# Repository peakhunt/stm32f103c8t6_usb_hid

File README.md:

# stm32f103c8t6_usb_hid

This is a USB joystick demo using STM32F103C8T6.
The whole project was developed using CubeMX.

## hardware
Basically I used very cheap chinese STM32F103 module. [The link is here][1]

As for arcade style joysticks and push buttons, there are a bunch of
cheap chinese stuffs out there.

As for connection, please refer to the kicad directory. It's gonna cost about $10 US dollars to get the 10 custom PCBs from cheap PCB manufactureres. Whether you use custom soldering or PCB based approach, just be sure to pay attention to the capacitor to prevent debouncing .  And just bear in mind that I am a S/W enginner. Designing a simple H/W like this is just a kind of my hobby.

[1]: https://www.aliexpress.com/item/Free-Shipping-STM32F103C8T6-ARM-STM32-Minimum-System-Development-Board-Module-For-arduino/32555258029.html?spm=2114.search0104.3.89.mrWsfD&ws_ab_test=searchweb0_0,searchweb201602_5_5460015_10152_10065_10151_10068_5470015_10307_10137_10060_10155_10154_10056_10055_10054_10059_100031_10099_10338_10339_5380015_10103_10102_440_10052_10053_10142_10107_10050_10051_10326_10084_10083_10080_10082_10081_10110_10175_10111_10112_10113_10114_143_10037_10312_10313_10314_10078_10079_10077_10073,searchweb201603_19,ppcSwitch_5&btsid=67a13b36-0190-4c70-9deb-1a2744050228&algo_expid=c62760bd-a140-4c3e-86ec-c725bdf3f0dc-14&algo_pvid=c62760bd-a140-4c3e-86ec-c725bdf3f0dc

## my build
Here is a demo joystick I built. I've been having some fun using it with retroarch. I love kungfu master.

The case is actually a small rectangular plastic container ( or basket or whatever). I bought it at less than 2 dollars at a local store and drilled it.

Here is the image of PCB I created for the build. It's really primitive simple board and anybody can do it. I just hated all the stupid fragile wiring I had to do before the PCB.

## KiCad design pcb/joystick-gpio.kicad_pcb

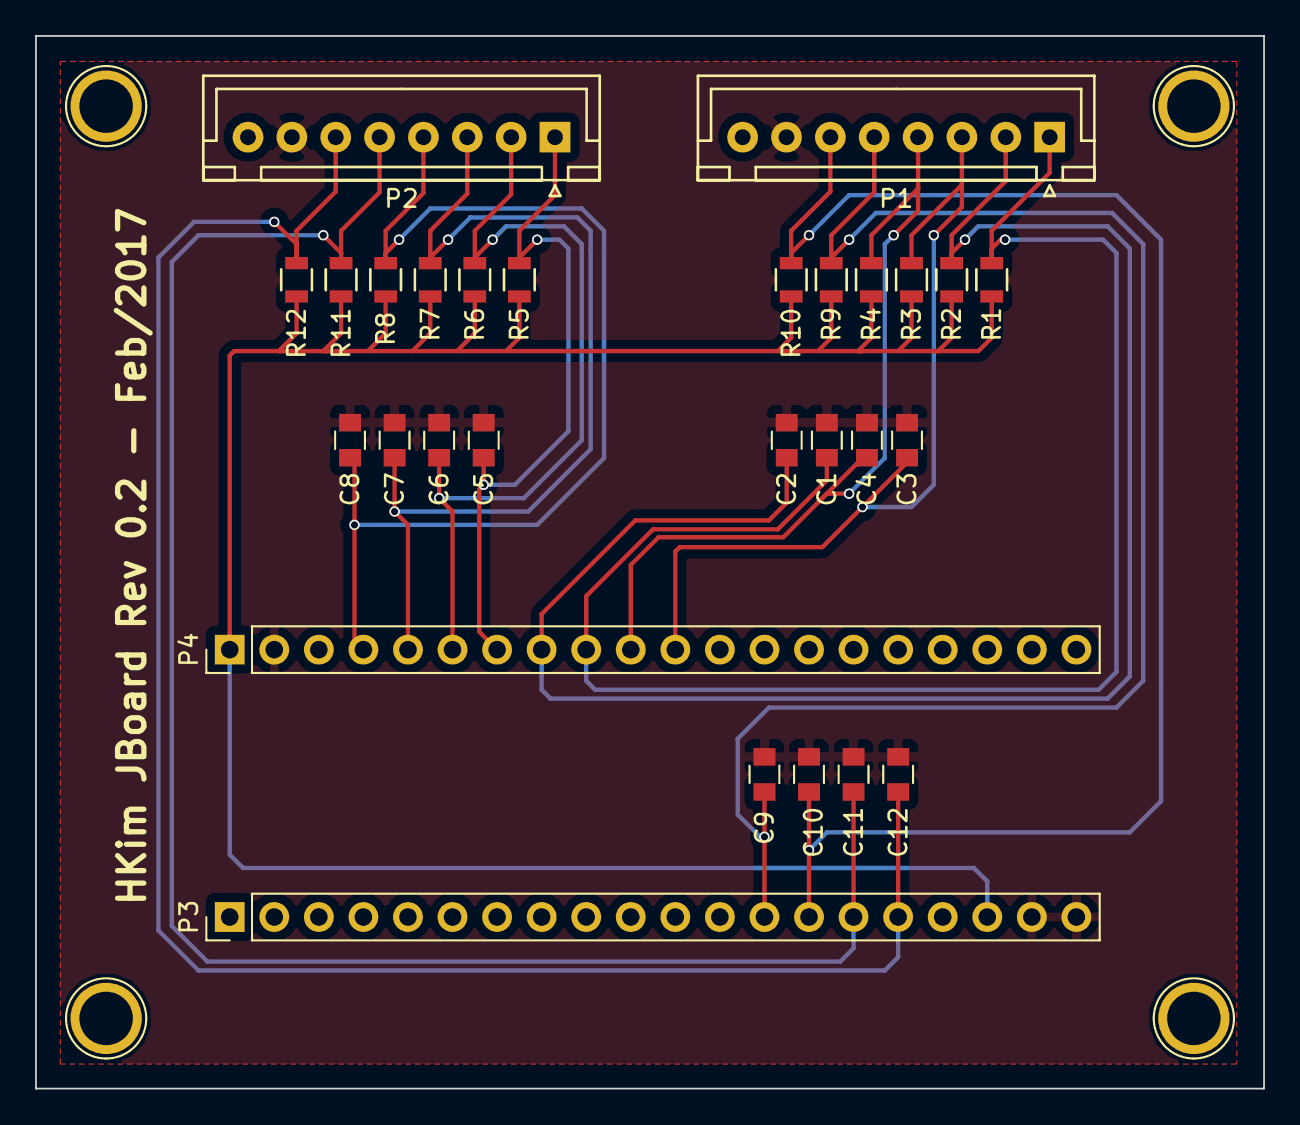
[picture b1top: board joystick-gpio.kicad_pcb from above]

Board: 2 copper layers, 70.0 x 60.0 mm, 28 parts (0 on the bottom side), 14 nets.

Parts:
C1, C2, C3, C4, C5, C6, C7, C8, C9, C10, C11, C12: 100nF; C_0805
P1, P2: CONN_01X08; JST_XH_B08B-XH-A_08x2.50mm_Straight
P3, P4: CONN_01X20; Socket_Strip_Straight_1x20_Pitch2.54mm
R1, R2, R3, R4, R5, R6, R7, R8, R9, R10, R11, R12: 47K; R_0805

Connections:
/3.3V: P3.18, P4.1, R1.2, R2.2, R3.2, R4.2, R5.2, R6.2, R7.2, R8.2, R9.2, R10.2, R11.2, R12.2
/GROUND: C1.1, C2.1, C3.1, C4.1, C5.1, C6.1, C7.1, C8.1, C9.1, C10.1, C11.1, C12.1, P1.7, P2.7, P3.19, P3.20, P4.2
/JBT0: C5.2, P2.1, P4.7, R5.1
/JBT1: C6.2, P2.2, P4.6, R6.1
/JBT2: C7.2, P2.3, P4.5, R7.1
/JBT3: C8.2, P2.4, P4.4, R8.1
/JBT4: C9.2, P1.5, P3.13, R9.1
/JBT5: C10.2, P1.6, P3.14, R10.1
/JDOWN: C2.2, P1.2, P4.8, R2.1
/JLEFT: C3.2, P1.3, P4.11, R3.1
/JRIGHT: C4.2, P1.4, P4.10, R4.1
/JSELECT: C12.2, P2.6, P3.16, R12.1
/JSTART: C11.2, P2.5, P3.15, R11.1
/JUP: C1.2, P1.1, P4.9, R1.1

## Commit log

2017-09-13 initial import
2017-09-13 removed AC6 residue
2017-09-13 adding kicad schematics
2017-09-16 adding sample pictures
2018-03-11 typo fix.
2018-08-08 changed to use USB HID report id
2022-05-13 it's been a while. a new mechanism
2022-05-13 minor code restructure
2022-05-13 readding simple old primitive pcb
2022-05-13 recovering images
2022-05-13 readme update
2022-05-13 code change to support dual joystick
2022-05-20 changed HID IN interrupt EP's max packet size to 4. still investigating why 64 isn't working
2022-05-20 solving max 64 bytes packet length problem
